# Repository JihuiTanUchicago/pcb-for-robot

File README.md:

# pcb_robo
This is a repo for my PCB design and engineering class where I made a PCB to talk to a TurtleBot3 and control its movement.

# Demo Video
- Youtube: https://youtu.be/oqg4fr0NS5o

# PCB

> **Note:** All components were hand-soldered onto the PCB board, including the SAMD21A(i know bruh it's HARD).

# KICAD PCB VIEW & SCHEMATICS
## PCB

## Schematics

# PCB - Robot Communication Pipeline

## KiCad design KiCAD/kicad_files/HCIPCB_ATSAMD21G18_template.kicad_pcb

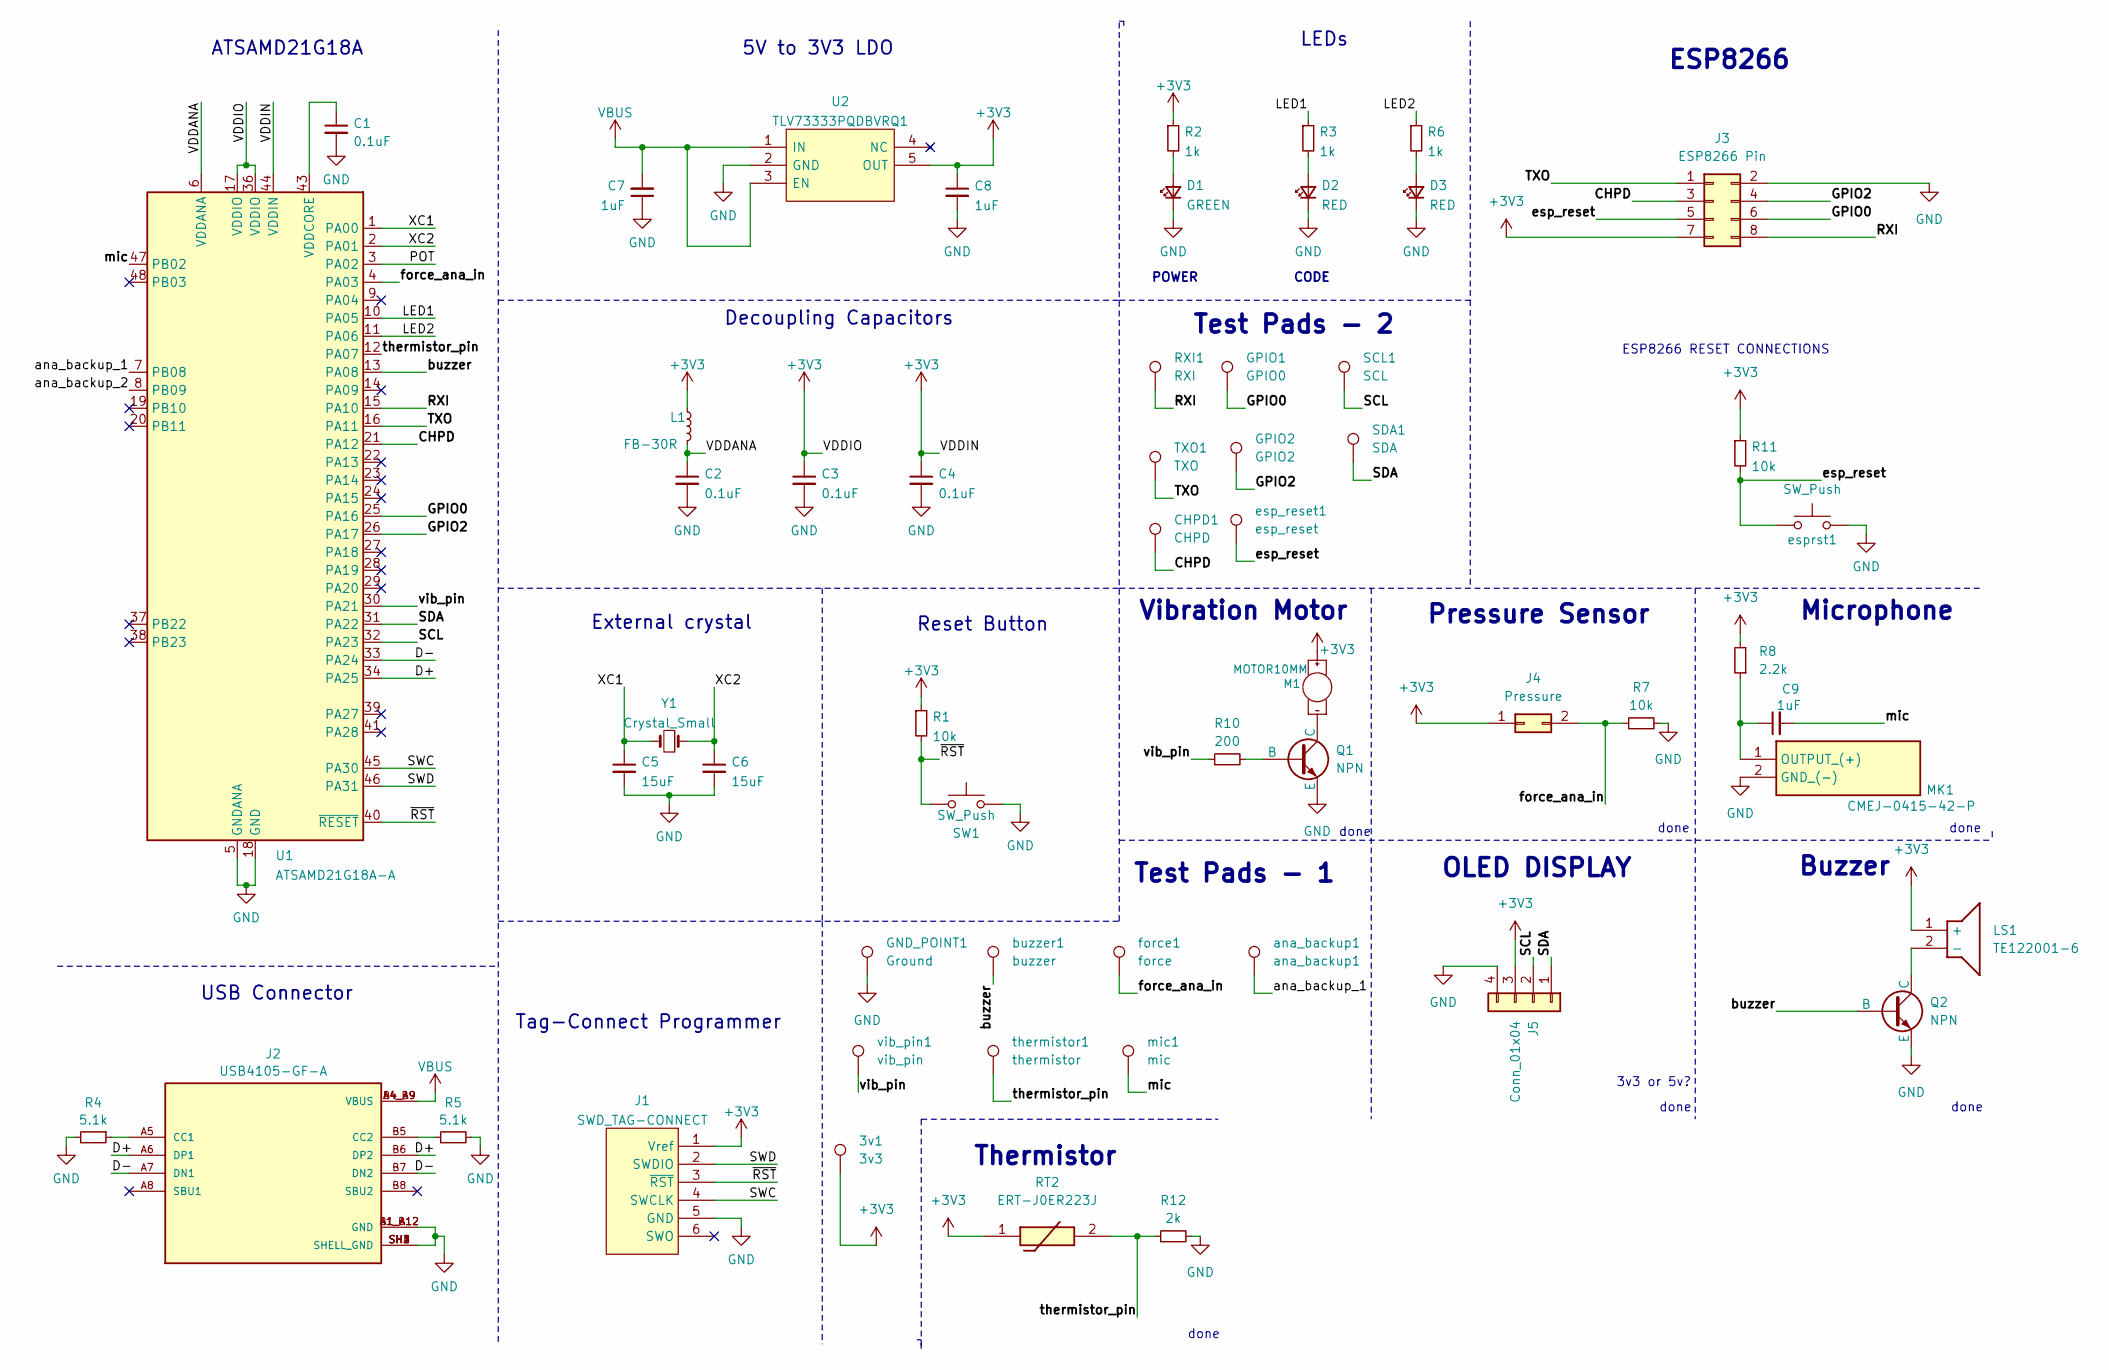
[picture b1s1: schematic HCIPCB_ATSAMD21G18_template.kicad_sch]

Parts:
3v1: 3v3; TestPoint_Pad_1.0x1.0mm
C1, C2, C3, C4: 0.1uF; C_0603_1608Metric_Pad1.08x0.95mm_HandSolder
C5, C6: 15uF; C_0603_1608Metric_Pad1.08x0.95mm_HandSolder
C7, C8, C9: 1uF; C_0603_1608Metric_Pad1.08x0.95mm_HandSolder
CHPD1: CHPD; TestPoint_Pad_1.0x1.0mm
D1: GREEN; LED_0603_1608Metric_Pad1.05x0.95mm_HandSolder
D2, D3: RED; LED_0603_1608Metric_Pad1.05x0.95mm_HandSolder
GND_POINT1: Ground; TestPoint_Pad_1.0x1.0mm
GPIO1: GPIO0; TestPoint_Pad_1.0x1.0mm
GPIO2: GPIO2; TestPoint_Pad_1.0x1.0mm
J1: SWD_TAG-CONNECT; Tag-Connect_TC2030-IDC-FP_2x03_P1.27mm_Vertical
J2: USB4105-GF-A; GCT_USB4105-GF-A
J3: ESP8266 Pin; PinSocket_2x04_P2.54mm_Vertical
J4: Pressure; PinSocket_2x01_P2.54mm_Vertical
J5: Conn_01x04; PinHeader_1x04_P2.54mm_Vertical
L1: FB-30R; L_0603_1608Metric_Pad1.05x0.95mm_HandSolder
LS1: TE122001-6; TE1220016; Mouser Part Number 497-TE122001-6
M1: MOTOR10MM; VIBE-MOTOR-10MM
MK1: CMEJ-0415-42-P; PinHeader_2x01_P1.00mm_Vertical; Mouser Part Number 490-CMEJ-0415-42-P
Q1, Q2: NPN; SOT-323_SC-70_Handsoldering
R1, R7, R11: 10k; R_0603_1608Metric_Pad0.98x0.95mm_HandSolder
R2, R3, R6: 1k; R_0603_1608Metric_Pad0.98x0.95mm_HandSolder
R4, R5: 5.1k; R_0603_1608Metric_Pad0.98x0.95mm_HandSolder
R8: 2.2k; R_0603_1608Metric_Pad0.98x0.95mm_HandSolder
R10: 200; R_0603_1608Metric_Pad0.98x0.95mm_HandSolder
R12: 2k; R_0603_1608Metric_Pad0.98x0.95mm_HandSolder
RT2: ERT-J0ER223J; PinHeader_2x01_P1.00mm_Vertical; Mouser Part Number 667-ERT-J0ER223J
RXI1: RXI; TestPoint_Pad_1.0x1.0mm
SCL1: SCL; TestPoint_Pad_1.0x1.0mm
SDA1: SDA; TestPoint_Pad_1.0x1.0mm
SW1: SW_Push; SW_SPST_TL3305A
TXO1: TXO; TestPoint_Pad_1.0x1.0mm
U1: ATSAMD21G18A-A; TQFP-48_7x7mm_P0.5mm
U2: TLV73333PQDBVRQ1; SOT95P280X145-5N; Mouser Part Number 595-TLV73333PQDBVRQ1
Y1: Crystal_Small; Crystal_SMD_3215-2Pin_3.2x1.5mm
ana_backup1: ana_backup1; TestPoint_Pad_1.0x1.0mm
buzzer1: buzzer; TestPoint_Pad_1.0x1.0mm
esp_reset1: esp_reset; TestPoint_Pad_1.0x1.0mm
esprst1: SW_Push; SW_SPST_TL3305A
force1: force; TestPoint_Pad_1.0x1.0mm
mic1: mic; TestPoint_Pad_1.0x1.0mm
thermistor1: thermistor; TestPoint_Pad_1.0x1.0mm
vib_pin1: vib_pin; TestPoint_Pad_1.0x1.0mm

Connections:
+3V3: 3v1.1, C3.1, C4.1, C8.1, J1.1 (Vref), J3.7, J4.1, J5.3, L1.1, LS1.1 (+), M1.+, R1.1, R2.1, R8.2, R11.1, RT2.1, U1.17 (VDDIO), U1.36 (VDDIO), U1.44 (VDDIN), U2.5 (OUT); also elsewhere on the board
/CHPD: CHPD1.1, J3.3, U1.21 (PA12)
/D+: J2.A6 (DP1), J2.B6 (DP2), U1.34 (PA25)
/D-: J2.A7 (DN1), J2.B7 (DN2), U1.33 (PA24)
/GPIO0: GPIO1.1, J3.6, U1.25 (PA16)
/GPIO2: GPIO2.1, J3.4, U1.26 (PA17)
/LED1: R3.1, U1.10 (PA05)
/LED2: R6.1, U1.11 (PA06)
/POT: U1.3 (PA02)
/RXI: J3.8, RXI1.1, U1.15 (PA10)
/SCL: J5.2, SCL1.1, U1.32 (PA23)
/SDA: J5.1, SDA1.1, U1.31 (PA22)
/SWC: J1.4 (SWCLK), U1.45 (PA30)
/SWD: J1.2 (SWDIO), U1.46 (PA31)
/TXO: J3.1, TXO1.1, U1.16 (PA11)
/VDDANA: C2.1, L1.2, U1.6 (VDDANA)
/XC1: C5.1, U1.1 (PA00), Y1.2
/XC2: C6.1, U1.2 (PA01), Y1.1
/ana_backup_1: U1.7 (PB08), ana_backup1.1
/ana_backup_2: U1.8 (PB09)
/buzzer: Q2.2 (B), U1.13 (PA08), buzzer1.1
/esp_reset: J3.5, R11.2, esp_reset1.1, esprst1.1
/force_ana_in: J4.2, R7.1, U1.4 (PA03), force1.1
/mic: C9.2, U1.47 (PB02), mic1.1
/thermistor_pin: R12.1, RT2.2, U1.12 (PA07), thermistor1.1; also elsewhere on the board
/vib_pin: R10.1, U1.30 (PA21), vib_pin1.1
/~RST: J1.3 (~RST), R1.2, SW1.1, U1.40 (~RESET)
GND: C1.2, C2.2, C3.2, C4.2, C5.2, C6.2, C7.1, C8.2, D1.1 (K), D2.1 (K), D3.1 (K), GND_POINT1.1, J1.5 (GND), J2.A1_B12 (GND), J2.B1_A12 (GND), J2.SH1 (SHELL_GND), J2.SH2 (SHELL_GND), J2.SH3 (SHELL_GND), J2.SH4 (SHELL_GND), J3.2, J5.4, MK1.2 (GND_(-)), Q1.3 (E), Q2.3 (E), R4.2, R5.2, R7.2, R12.2, SW1.2, U1.5 (GNDANA), U1.18 (GND), U1.35 (GND), U1.42 (GND), U2.2 (GND), esprst1.2; also elsewhere on the board
unnamed: D1.2 (A), R2.2
unnamed: D2.2 (A), R3.2
unnamed: D3.2 (A), R6.2
unnamed: J2.A5 (CC1), R4.1
unnamed: J2.B5 (CC2), R5.1
unnamed: LS1.2 (-), Q2.1 (C)
unnamed: C9.1, MK1.1 (OUTPUT_(+)), R8.1
unnamed: Q1.2 (B), R10.2
unnamed: M1.-, Q1.1 (C)
unnamed: C1.1, U1.43 (VDDCORE)
VBUS: C7.2, J2.A4_B9 (VBUS), J2.B4_A9 (VBUS), U2.1 (IN), U2.3 (EN)

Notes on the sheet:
5V to 3V3 LDO
3v3 or 5v?
External crystal
OLED DISPLAY
Thermistor
Test Pads - 2
Tag-Connect Programmer
Decoupling Capacitors
done
ESP8266 RESET CONNECTIONS
CODE
Test Pads - 1
Microphone
Buzzer
LEDs
Pressure Sensor
POWER
ESP8266
Vibration Motor
USB Connector
ATSAMD21G18A
Reset Button

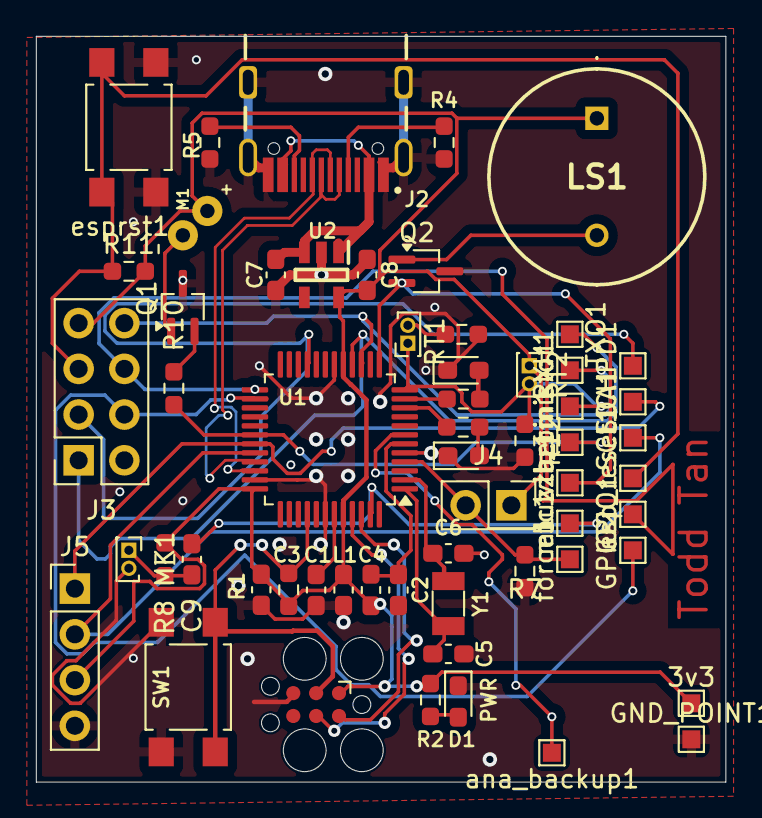
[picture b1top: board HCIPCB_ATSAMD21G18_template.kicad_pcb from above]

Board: 2 copper layers, 38.3 x 41.4 mm, 58 parts (0 on the bottom side), 38 nets.

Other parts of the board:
3v3: 3v3; TestPoint_Pad_1.0x1.0mm
R9: 750; R_0603_1608Metric_Pad0.98x0.95mm_HandSolder
RT1: ERT-J0ER223J; PinHeader_2x01_P1.00mm_Vertical

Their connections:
+3V3: 3v3.1; also elsewhere on the board
/thermistor_pin: RT1.1; also elsewhere on the board
GND: R9.2; also elsewhere on the board
unnamed: R9.1, RT1.2

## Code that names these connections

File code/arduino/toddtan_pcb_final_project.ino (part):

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  0b00000000, 0b00110000 };
//=================================================
//======/Buzzer Logic =============================
const int buzzer = 4;
int buzzer_is_high = false;
unsigned long buzzer_last_time = millis();
unsigned long buzzer_current_time = millis();
//=================================================
//======/LEDs Logic =============================
const int led1 = 18;
const int led2 = 8;
int led_state = 0;
int led_is_high = false;
unsigned long led_last_time = millis();
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  SerialUSB.println("Begin Setup");
  Serial1.begin(115200);
  delay(1000);
  pinMode(buzzer, OUTPUT);
  pinMode(led1, OUTPUT);
  pinMode(led2, OUTPUT);
  pinMode(vibrator, OUTPUT);
  // SSD1306_SWITCHCAPVCC = generate display voltage from 3.3V internally
  if(!display.begin(SSD1306_SWITCHCAPVCC, SCREEN_ADDRESS)) {
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
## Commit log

2024-05-19 project upload
